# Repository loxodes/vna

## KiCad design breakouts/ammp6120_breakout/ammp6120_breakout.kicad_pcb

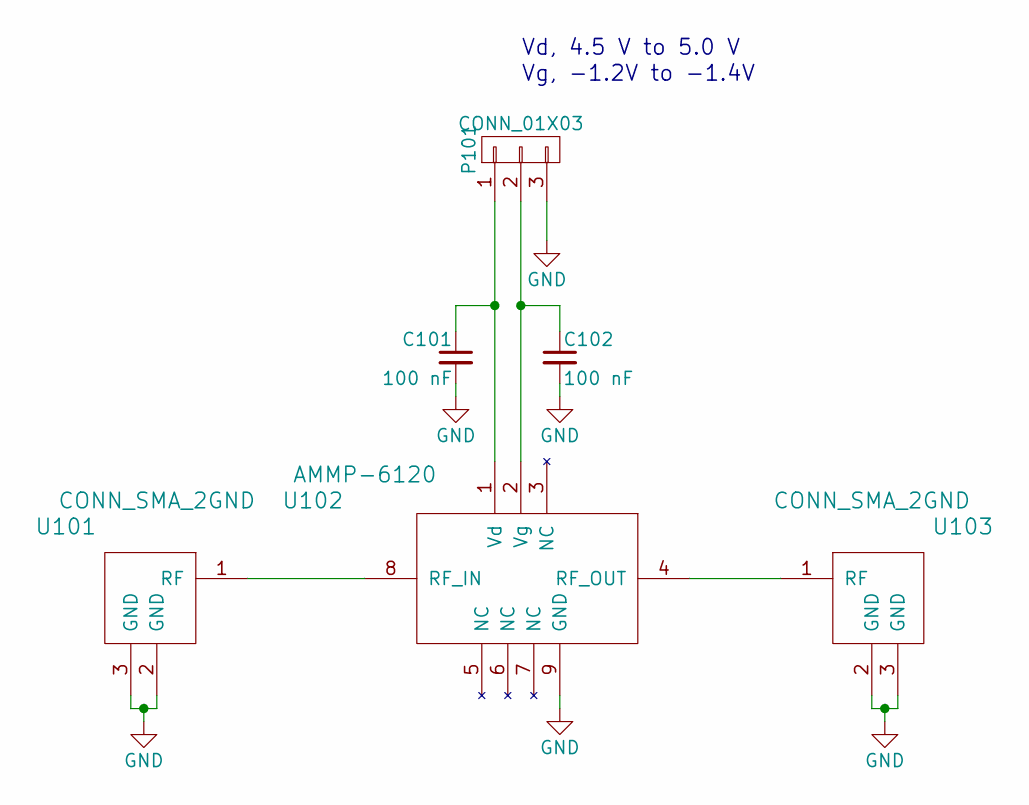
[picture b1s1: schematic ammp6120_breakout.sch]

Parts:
C101, C102: 100 nF; C_0402
P101: CONN_01X03; Pin_Header_Straight_1x03
U101, U103: CONN_SMA_2GND; SMA_CPW_1MM_.2MM
U102: AMMP-6120; 8QFN_5mm

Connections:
GND: C101.2, C102.2, P101.3, U101.2 (GND), U101.3 (GND), U102.9 (GND), U103.2 (GND), U103.3 (GND)
unnamed: C101.1, P101.1, U102.1 (Vd)
unnamed: C102.1, P101.2, U102.2 (Vg)
unnamed: U101.1 (RF), U102.8 (RF_IN)
unnamed: U102.4 (RF_OUT), U103.1 (RF)

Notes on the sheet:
Vg, -1.2V to -1.4V
Vd, 4.5 V to 5.0 V

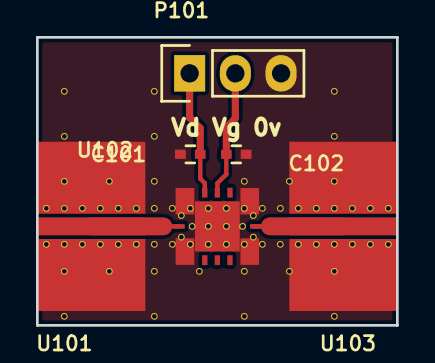
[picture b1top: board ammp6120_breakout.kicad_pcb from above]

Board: 4 copper layers, 20.0 x 16.0 mm, 6 parts (0 on the bottom side), 5 nets.

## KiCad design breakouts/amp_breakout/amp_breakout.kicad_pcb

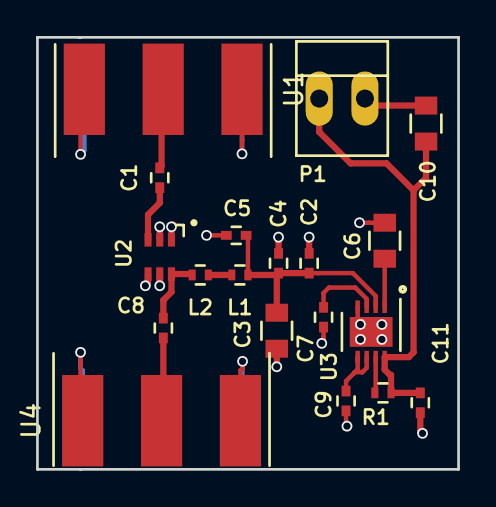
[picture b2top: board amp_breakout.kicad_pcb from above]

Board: 4 copper layers, 23.4 x 24.0 mm, 19 parts (0 on the bottom side), 12 nets.

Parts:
C1, C5, C8, C11: 1 nF; C_0402
C2: 100 pF; C_0402
C3, C6, C10: 10 uF; C_0805
C4, C7, C9: 1 uF; C_0402
L1: 56 nH; R_0402
L2: 6 nH; R_0402
P1: CONN_01X02; PINHEAD1-2
R1: 0; R_0402
U1, U4: CONN_SMA; 732511150_sma
U2: MGA-82563; SC-70-6
U3: ADM7150; DFN-8-1EP_3x3mm_Pitch0.5mm

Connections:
GND: C2.1, C3.1, C4.1, C5.1, C6.1, C7.1, C9.1, C10.1, C11.1, P1.2, U1.2, U1.3, U1.4, U1.5, U2.1, U2.2, U2.4, U2.5, U3.4, U3.9, U4.2, U4.3, U4.4, U4.5
unnamed: C1.1, U2.3
unnamed: C1.2, U1.1
unnamed: C2.2, C3.2, C4.2, C5.2, L1.1, U3.2
unnamed: C6.2, U3.1
unnamed: C7.2, U3.3
unnamed: C8.1, U4.1
unnamed: C8.2, L2.2, U2.6
unnamed: C9.2, U3.5, U3.6
unnamed: C10.2, C11.2, P1.1, R1.1, U3.8
unnamed: L1.2, L2.1
unnamed: R1.2, U3.7

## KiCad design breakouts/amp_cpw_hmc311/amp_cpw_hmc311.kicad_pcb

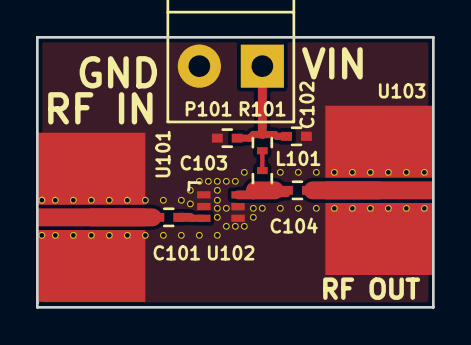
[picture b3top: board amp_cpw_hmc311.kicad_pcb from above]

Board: 4 copper layers, 22.0 x 15.0 mm, 10 parts (0 on the bottom side), 7 nets.

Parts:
C101, C102, C104: 100 pF; C_0402
C103: .01 uF; C_0402
L101: 18 nH; R_0402
P101: CONN_01X02; TerminalBlock_Pheonix_PT-3.5mm_2pol
R101: 22; R_0402
U101, U103: CONN_SMA; SMA_CPW_1MM_.2MM
U102: HMC311SC70; SC-70-6

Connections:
GND: C102.2, C103.2, P101.2, U101.2, U101.3, U102.1, U102.2, U102.4, U102.5, U103.2, U103.3
unnamed: C101.1, U102.3
unnamed: C101.2, U101.1
unnamed: C102.1, C103.1, P101.1, R101.1
unnamed: C104.1, U103.1
unnamed: C104.2, L101.2, U102.6
unnamed: L101.1, R101.2

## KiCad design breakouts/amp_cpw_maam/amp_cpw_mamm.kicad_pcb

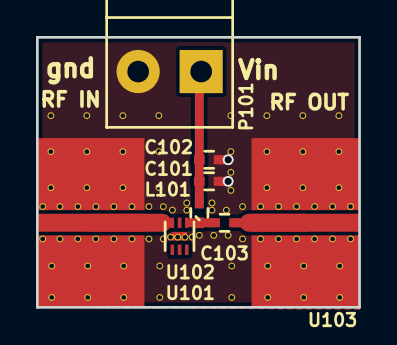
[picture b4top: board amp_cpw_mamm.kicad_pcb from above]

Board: 4 copper layers, 17.9 x 15.0 mm, 8 parts (0 on the bottom side), 5 nets.

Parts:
C101: 100 nF; C_0402
C102, C103: 100 pF; C_0402
L101: BLM15GG471; C_0402
P101: CONN_01X02; TerminalBlock_Pheonix_PT-3.5mm_2pol
U101, U103: CONN_SMA; SMA_CPW_1MM_.2MM
U102: MAAM-011101; TDFN6

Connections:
GND: C101.2, C102.2, P101.2, U101.2, U101.3, U102.7, U103.2, U103.3
unnamed: C101.1, C102.1, L101.2, P101.1
unnamed: C103.1, U103.1
unnamed: C103.2, L101.1, U102.1
unnamed: U101.1, U102.3

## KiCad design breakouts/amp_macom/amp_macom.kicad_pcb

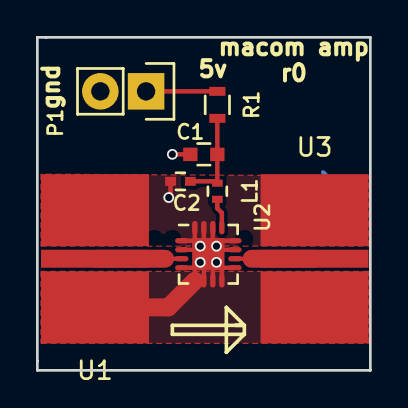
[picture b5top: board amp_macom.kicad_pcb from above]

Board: 4 copper layers, 18.5 x 18.5 mm, 8 parts (0 on the bottom side), 6 nets.

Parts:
C1: 1 uF; C_0603
C2: 10 pF; C_0402
L1: L_Small; R_0402
P1: CONN_01X02; Pin_Header_Straight_1x02
R1: R_Small; R_0603
U1, U3: CONN_SMA; SMA_CPW_1MM_.2MM
U2: CMM0511-QT-0G0T; QFN-16-1EP_3x3mm_Pitch0.5mm

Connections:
GND: C1.2, C2.2, P1.2, U1.2, U1.3, U2.1, U2.2, U2.4, U2.5, U2.6, U2.7, U2.8, U2.9, U2.11, U2.12, U2.14, U2.15, U2.16, U2.17, U3.2, U3.3
unnamed: C1.1, C2.1, L1.1, R1.2
unnamed: L1.2, U2.13
unnamed: P1.1, R1.1
unnamed: U1.1, U2.3
unnamed: U2.10, U3.1

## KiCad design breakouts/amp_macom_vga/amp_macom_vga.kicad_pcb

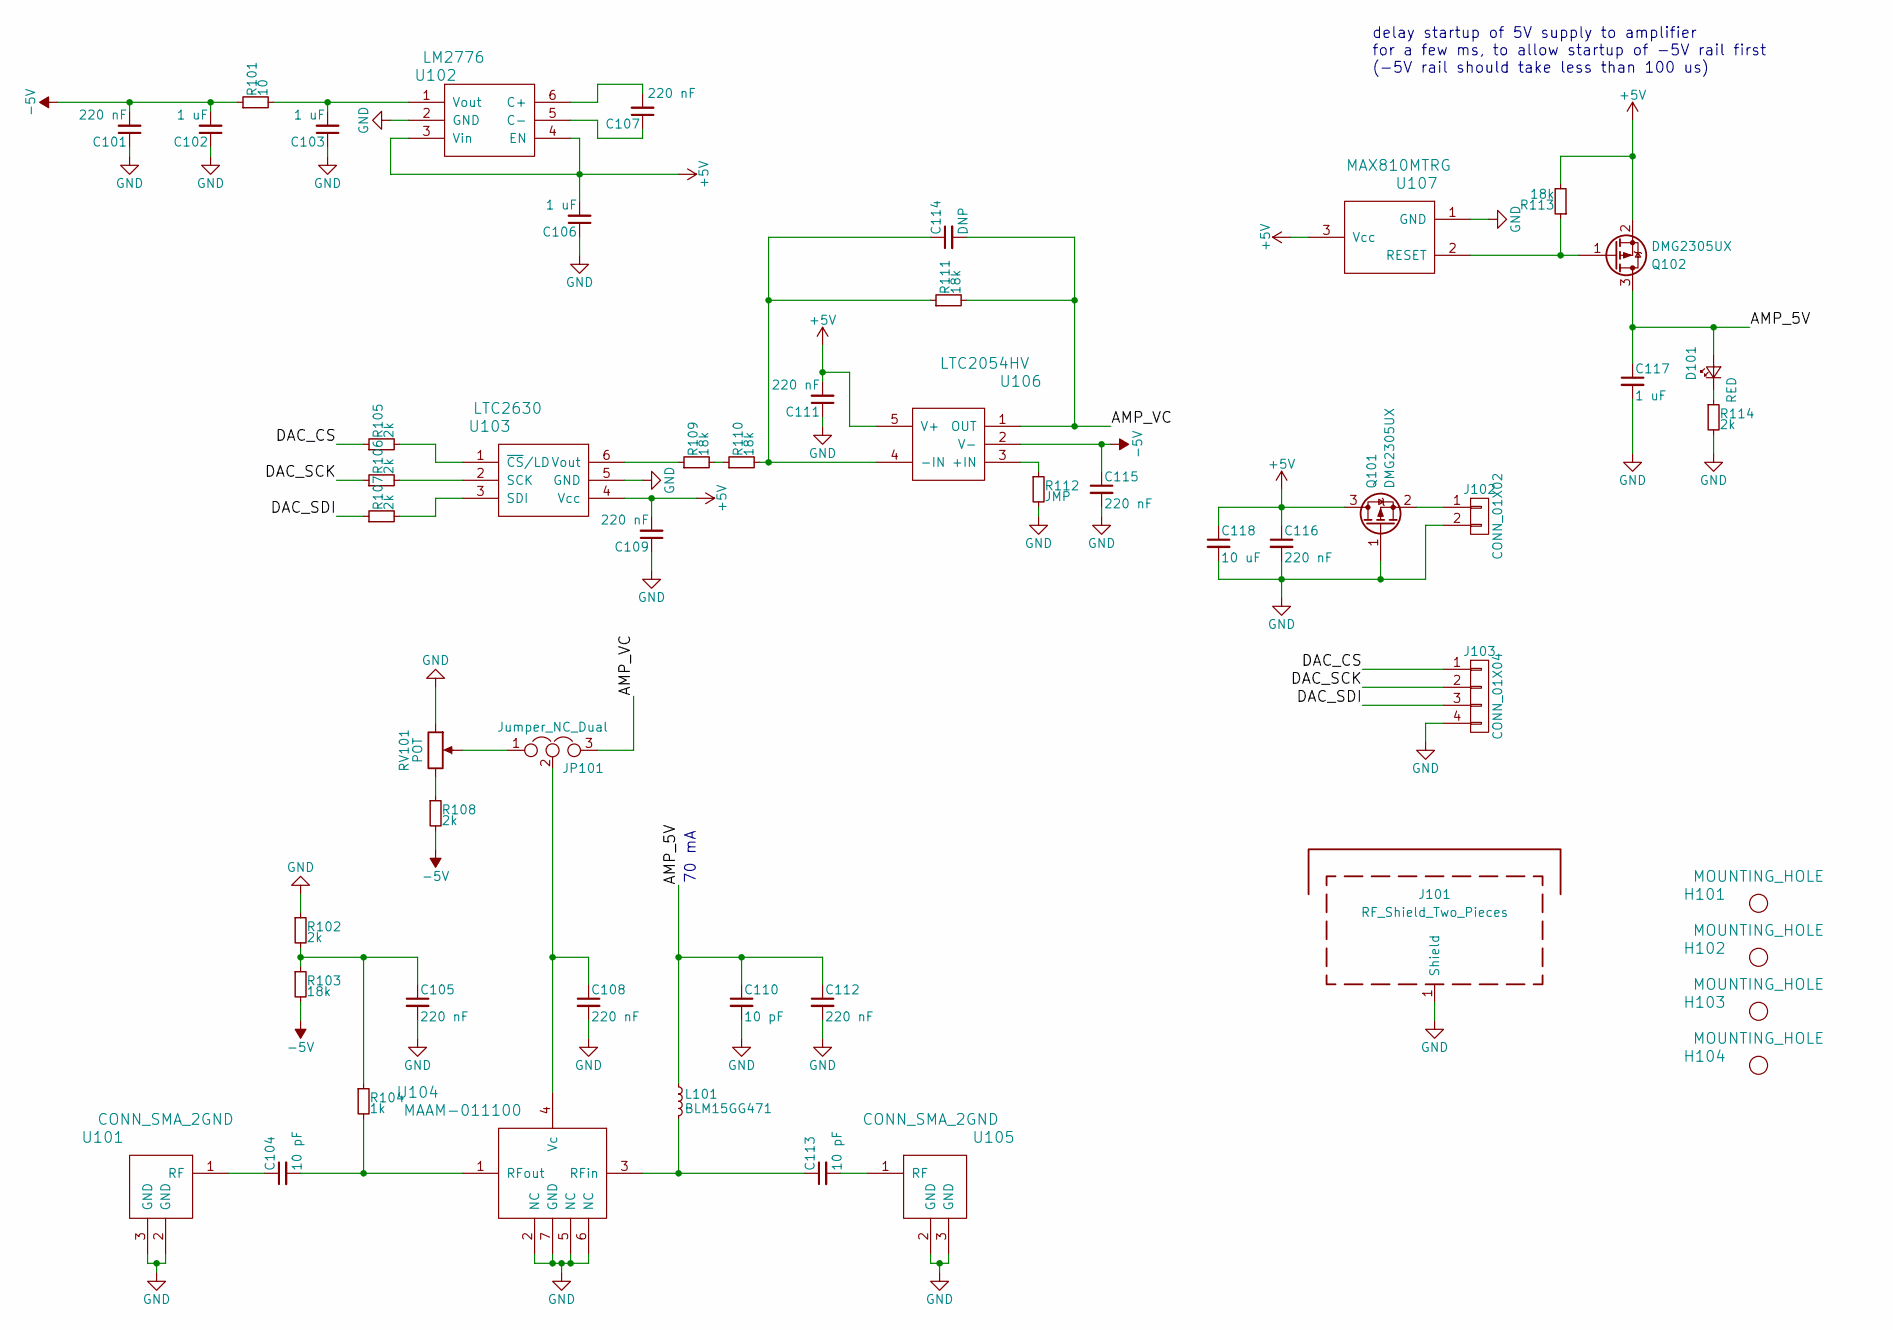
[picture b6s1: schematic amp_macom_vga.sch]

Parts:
C101, C105, C107, C108, C109, C111, C112, C115, C116: 220 nF; C_0402
C102, C103, C106, C117: 1 uF; C_0603
C104, C110, C113: 10 pF; C_0402
C114: DNP; C_0402
C118: 10 uF; C_0603
D101: RED; LED_0603
H101, H102, H103, H104: MOUNTING_HOLE; MountingHole_2-7mm
J101: RF_Shield_Two_Pieces; Laird_Technologies_BMI-S-201-F_13.66x12.70mm
J102: CONN_01X02; TerminalBlock_Pheonix_MPT-2.54mm_2pol
J103: CONN_01X04; Pin_Header_Straight_1x04
JP101: Jumper_NC_Dual; JMP_3
L101: BLM15GG471; R_0402
Q101, Q102: DMG2305UX; SOT-23
R101: 10; R_0402
R102, R105, R106, R107, R108, R114: 2k; R_0402
R103, R109, R110, R111, R113: 18k; R_0402
R104: 1k; R_0402
R112: JMP; R_0402
RV101: POT; POT_SMD
U101, U105: CONN_SMA_2GND; SMA_901-10512_6p7MIL_FR408_CPW_LAUNCH
U102: LM2776; SOT-23-6
U103: LTC2630; SC-70-6
U104: MAAM-011100; TDFN6
U106: LTC2054HV; SOT-23-5
U107: MAX810MTRG; SOT-23

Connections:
+5V: C106.2, C109.2, C111.2, C116.1, C118.1, Q101.3 (D), Q102.2 (S), R113.2, U102.3 (Vin), U102.4 (EN), U103.4 (Vcc), U106.5 (V+), U107.3 (Vcc)
-5V: C101.2, C102.2, C115.1, R101.1, R103.2, R108.2, U106.2 (V-)
/AMP_5V: C110.1, C112.1, C117.1, D101.2 (A), L101.1, Q102.3 (D)
/AMP_VC: C114.2, JP101.3, R111.2, U106.1 (OUT)
/DAC_CS: J103.1, R105.1
/DAC_SCK: J103.2, R106.1
/DAC_SDI: J103.3, R107.1
GND: C101.1, C102.1, C103.1, C105.2, C106.1, C108.2, C109.1, C110.2, C111.1, C112.2, C115.2, C116.2, C117.2, C118.2, J101.1, J102.2, J103.4, Q101.1 (G), R102.1, R112.2, R114.2, RV101.1, U101.2 (GND), U101.3 (GND), U102.2 (GND), U103.5 (GND), U104.2 (NC), U104.5 (NC), U104.6 (NC), U104.7 (GND), U105.2 (GND), U105.3 (GND), U107.1 (GND)
unnamed: C103.2, R101.2, U102.1 (Vout)
unnamed: C104.1, U101.1 (RF)
unnamed: C104.2, R104.2, U104.1 (RFout)
unnamed: C105.1, R102.2, R103.1, R104.1
unnamed: C107.1, U102.5 (C-)
unnamed: C107.2, U102.6 (C+)
unnamed: C108.1, JP101.2, U104.4 (Vc)
unnamed: C113.1, L101.2, U104.3 (RFin)
unnamed: C113.2, U105.1 (RF)
unnamed: C114.1, R110.2, R111.1, U106.4 (-IN)
unnamed: D101.1 (K), R114.1
unnamed: J102.1, Q101.2 (S)
unnamed: JP101.1, RV101.2
unnamed: Q102.1 (G), R113.1, U107.2 (RESET)
unnamed: R105.2, U103.1 (~CS~/LD)
unnamed: R106.2, U103.2 (SCK)
unnamed: R107.2, U103.3 (SDI)
unnamed: R108.1, RV101.3
unnamed: R109.1, U103.6 (Vout)
unnamed: R109.2, R110.1
unnamed: R112.1, U106.3 (+IN)

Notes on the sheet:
70 mA
delay startup of 5V supply to amplifier for a few ms, to allow startup of -5V rail first (-5V rail should take less than 100 us)

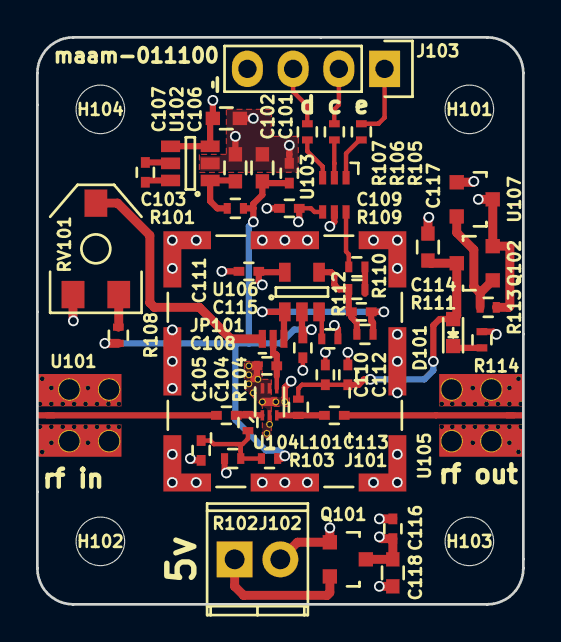
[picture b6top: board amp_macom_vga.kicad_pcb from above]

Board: 4 copper layers, 27.0 x 31.5 mm, 52 parts (0 on the bottom side), 29 nets.

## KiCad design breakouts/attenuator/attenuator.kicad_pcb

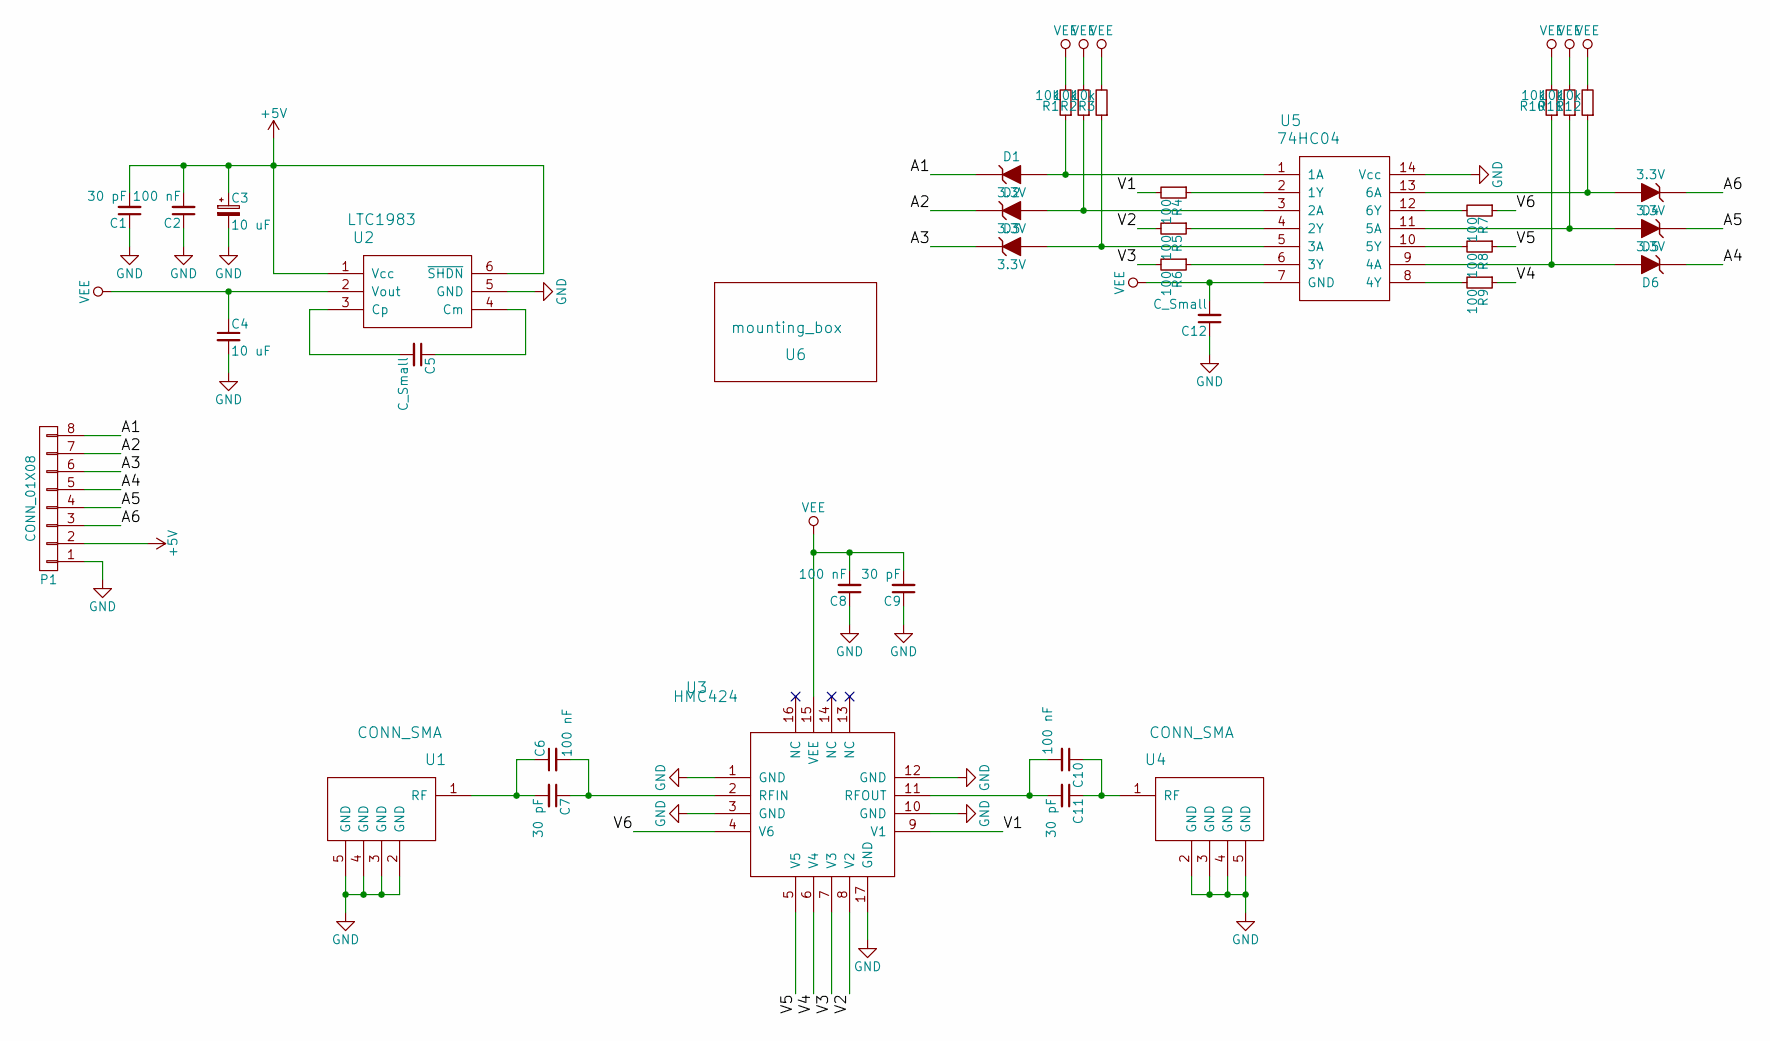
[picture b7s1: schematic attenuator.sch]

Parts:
C1, C7, C9, C11: 30 pF; C_0402
C2, C6, C8, C10: 100 nF; C_0402
C3, C4: 10 uF; C_0805
C5: C_Small; C_0805
C12: C_Small; C_0402
D1, D2, D3, D4, D5, D6: 3.3V; SOD-123
P1: CONN_01X08; Pin_Header_Straight_1x08
R1, R2, R3, R10, R11, R12: 10k; R_0402
R4, R5, R6, R7, R8, R9: 100; R_0402
U1, U4: CONN_SMA; 732512200_SMA
U2: LTC1983; SOT-23-6
U3: HMC424; QFN-16-1EP_3x3mm_Pitch0.5mm
U5: 74HC04; TSSOP-14_4.4x5mm_Pitch0.65mm
U6: mounting_box; POMONA_2400BOX

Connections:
+5V: C1.2, C2.2, C3.1, P1.2, U2.1 (Vcc), U2.6 (~SHDN)
/A1: D1.1 (K), P1.8
/A2: D2.1 (K), P1.7
/A3: D3.1 (K), P1.6
/A4: D6.1 (K), P1.5
/A5: D5.1 (K), P1.4
/A6: D4.1 (K), P1.3
/V1: R4.2, U3.9 (V1)
/V2: R5.2, U3.8 (V2)
/V3: R6.2, U3.7 (V3)
/V4: R9.1, U3.6 (V4)
/V5: R8.1, U3.5 (V5)
/V6: R7.1, U3.4 (V6)
GND: C1.1, C2.1, C3.2, C4.2, C8.1, C9.1, C12.1, P1.1, U1.2 (GND), U1.3 (GND), U1.4 (GND), U1.5 (GND), U2.5 (GND), U3.1 (GND), U3.3 (GND), U3.10 (GND), U3.12 (GND), U3.17 (GND), U4.2 (GND), U4.3 (GND), U4.4 (GND), U4.5 (GND), U5.14 (Vcc)
unnamed: C5.1, U2.4 (Cm)
unnamed: C5.2, U2.3 (Cp)
unnamed: C6.1, C7.2, U1.1 (RF)
unnamed: C6.2, C7.1, U3.2 (RFIN)
unnamed: C10.1, C11.1, U4.1 (RF)
unnamed: C10.2, C11.2, U3.11 (RFOUT)
unnamed: D1.2 (A), R1.1, U5.1 (1A)
unnamed: D2.2 (A), R2.1, U5.3 (2A)
unnamed: D3.2 (A), R3.1, U5.5 (3A)
unnamed: D4.2 (A), R12.1, U5.13 (6A)
unnamed: D5.2 (A), R11.1, U5.11 (5A)
unnamed: D6.2 (A), R10.1, U5.9 (4A)
unnamed: R4.1, U5.2 (1Y)
unnamed: R5.1, U5.4 (2Y)
unnamed: R6.1, U5.6 (3Y)
unnamed: R7.2, U5.12 (6Y)
unnamed: R8.2, U5.10 (5Y)
unnamed: R9.2, U5.8 (4Y)
VEE: C4.1, C8.2, C9.2, C12.2, R1.2, R2.2, R3.2, R10.2, R11.2, R12.2, U2.2 (Vout), U3.15 (VEE), U5.7 (GND)

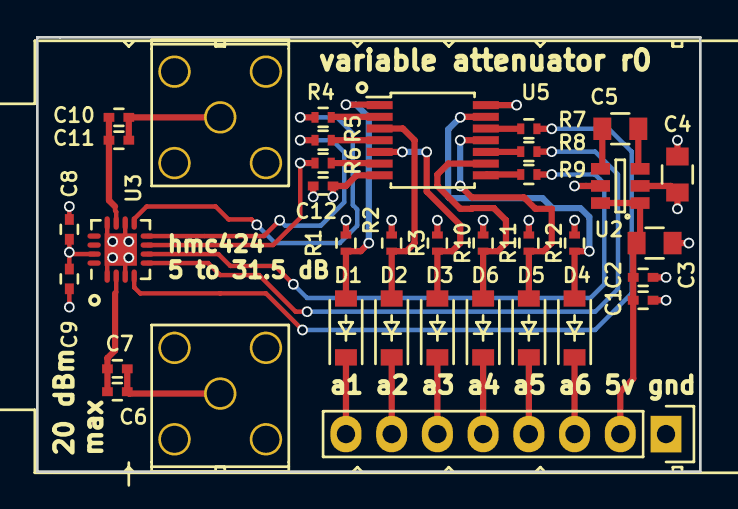
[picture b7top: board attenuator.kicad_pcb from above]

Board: 4 copper layers, 36.8 x 24.1 mm, 37 parts (0 on the bottom side), 33 nets.

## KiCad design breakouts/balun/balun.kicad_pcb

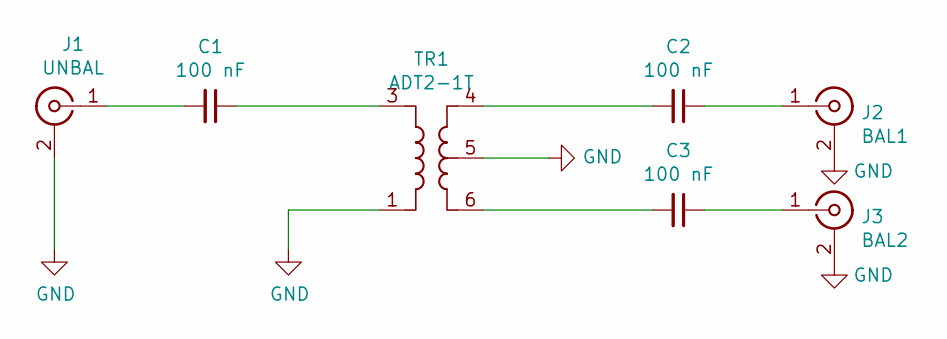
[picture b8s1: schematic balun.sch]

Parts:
C1, C2, C3: 100 nF; C_0603_1608Metric
J1: UNBAL; SMA_Amphenol_132134_Vertical
J2: BAL1; SMA_Amphenol_132134_Vertical
J3: BAL2; SMA_Amphenol_132134_Vertical
TR1: ADT2-1T; Mini-Circuits_CD542_H2.84mm

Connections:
GND: J1.2 (Ext), J2.2 (Ext), J3.2 (Ext), TR1.1, TR1.5
unnamed: C1.1, TR1.3
unnamed: C1.2, J1.1 (In)
unnamed: C2.1, J2.1 (In)
unnamed: C2.2, TR1.4
unnamed: C3.1, J3.1 (In)
unnamed: C3.2, TR1.6

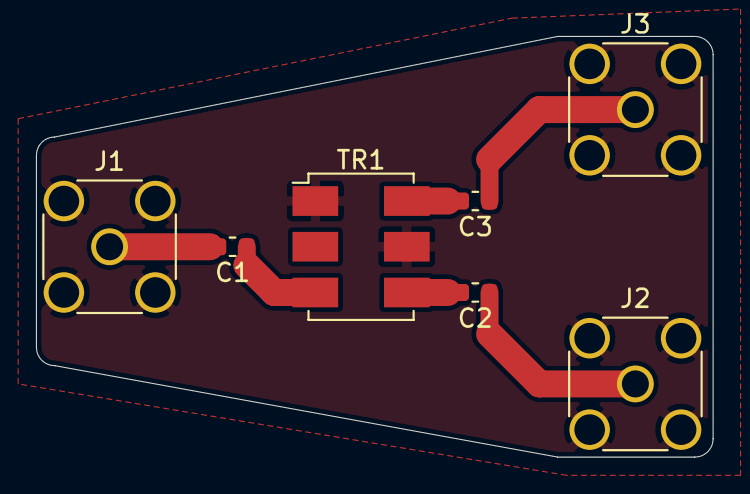
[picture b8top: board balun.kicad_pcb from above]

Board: 2 copper layers, 37.6 x 23.4 mm, 7 parts (0 on the bottom side), 7 nets.
